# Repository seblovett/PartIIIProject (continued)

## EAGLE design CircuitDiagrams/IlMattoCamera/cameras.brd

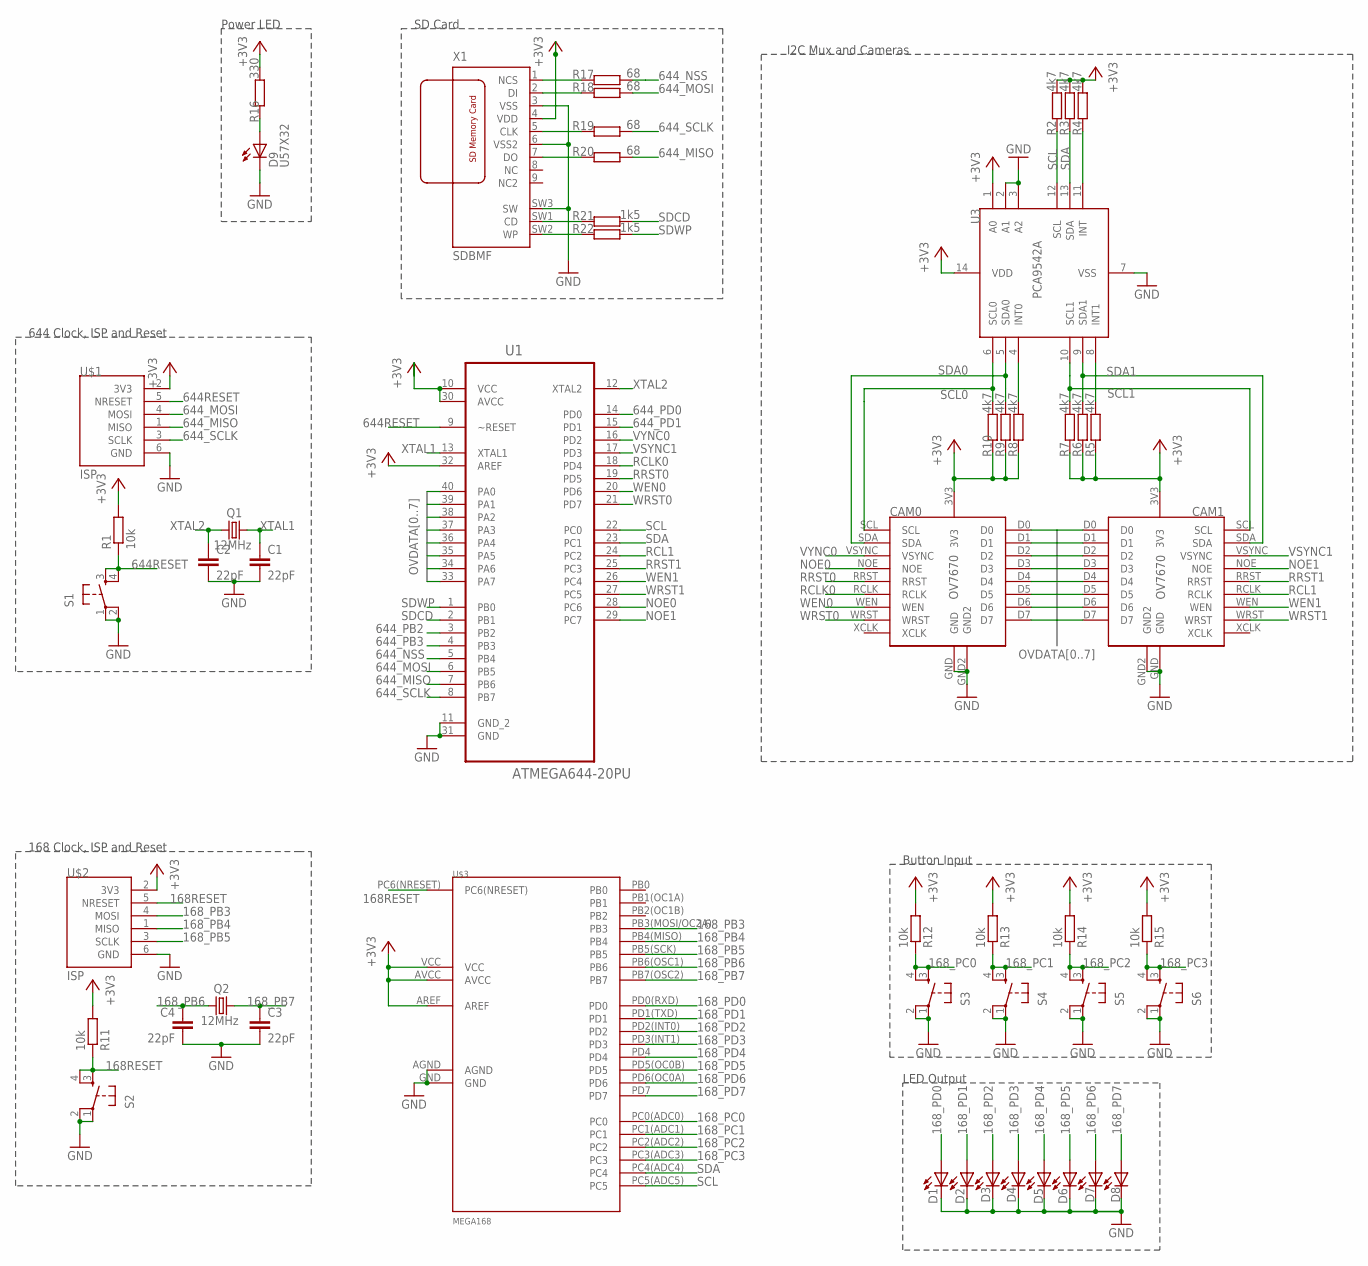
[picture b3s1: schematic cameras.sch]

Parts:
C1, C2, C3, C4: 22pF; C025-040X050
CAM0, CAM1: OV7670
D1, D2, D3, D4, D5, D6, D7, D8, D9: U57X32
Q1, Q2: 12MHz; HC49/S
R1, R11, R12, R13, R14, R15: 10k; 0204/7
R2, R3, R4, R5, R6, R7, R8, R9, R10: 4k7; 0204/7
R16: 330; 0204/7
R17, R18, R19, R20: 68; 0204/7
R21, R22: 1k5; 0204/7
S1, S2, S3, S4, S5, S6: TAC_SWITCHPTH; TACTILE-PTH
U1: ATMEGA644-20PU; DIP254P1524X482-40
U3: PCA9542A; TSSOP14
U$1, U$2: ISP; DUALHEAD_TH_6
U$3: MEGA168
X1: SDBMF; SDBMF-009XXBXX2

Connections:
168RESET: R11.1, S2.3, S2.4, U$2.5 (NRESET), U$3.PC6(NRESET)
168_PB3: U$2.4 (MOSI), U$3.PB3(MOSI/OC2A) (PB3)
168_PB4: U$2.1 (MISO), U$3.PB4(MISO) (PB4)
168_PB5: U$2.3 (SCLK), U$3.PB5(SCK) (PB5)
168_PB6: C4.1, Q2.1, U$3.PB6(OSC1) (PB6)
168_PB7: C3.1, Q2.2, U$3.PB7(OSC2) (PB7)
168_PC0: R12.1, S3.3, S3.4, U$3.PC0(ADC0) (PC0)
168_PC1: R13.1, S4.3, S4.4, U$3.PC1(ADC1) (PC1)
168_PC2: R14.1, S5.3, S5.4, U$3.PC2(ADC2) (PC2)
168_PC3: R15.1, S6.3, S6.4, U$3.PC3(ADC3) (PC3)
168_PD0: D1.A, U$3.PD0(RXD) (PD0)
168_PD1: D2.A, U$3.PD1(TXD) (PD1)
168_PD2: D3.A, U$3.PD2(INT0) (PD2)
168_PD3: D4.A, U$3.PD3(INT1) (PD3)
168_PD4: D5.A, U$3.PD4
168_PD5: D6.A, U$3.PD5(OC0B) (PD5)
168_PD6: D7.A, U$3.PD6(OC0A) (PD6)
168_PD7: D8.A, U$3.PD7
644RESET: R1.1, S1.3, S1.4, U1.9 (~RESET), U$1.5 (NRESET)
644_MISO: R20.1, U1.7 (PB6), U$1.1 (MISO)
644_MOSI: R18.1, U1.6 (PB5), U$1.4 (MOSI)
644_NSS: R17.1, U1.5 (PB4)
644_PB2: U1.3 (PB2)
644_PB3: U1.4 (PB3)
644_PD0: U1.14 (PD0)
644_PD1: U1.15 (PD1)
644_SCLK: R19.1, U1.8 (PB7), U$1.3 (SCLK)
+3V3: CAM0.3V3, CAM1.3V3, R1.2, R2.2, R3.2, R4.2, R5.1, R6.1, R7.1, R8.1, R9.1, R10.1, R11.2, R12.2, R13.2, R14.2, R15.2, R16.2, U1.10 (VCC), U1.30 (AVCC), U1.32 (AREF), U3.1 (A0), U3.14 (VDD), U$1.2 (3V3), U$2.2 (3V3), U$3.AREF, U$3.AVCC, U$3.VCC, X1.4 (VDD)
GND: C1.2, C2.2, C3.2, C4.2, CAM0.GND, CAM0.GND2, CAM1.GND, CAM1.GND2, D1.K (C), D2.K (C), D3.K (C), D4.K (C), D5.K (C), D6.K (C), D7.K (C), D8.K (C), D9.K (C), S1.1, S1.2, S2.1, S2.2, S3.1, S3.2, S4.1, S4.2, S5.1, S5.2, S6.1, S6.2, U1.11 (GND_2), U1.31 (GND), U3.2 (A1), U3.3 (A2), U3.7 (VSS), U$1.6 (GND), U$2.6 (GND), U$3.AGND, U$3.GND, X1.3 (VSS), X1.6 (VSS2), X1.SW3 (SW)
unnamed: R5.2, U3.8 (INT1)
unnamed: R8.2, U3.4 (INT0)
unnamed: R4.1, U3.11 (INT)
unnamed: R17.2, X1.1 (NCS)
unnamed: R18.2, X1.2 (DI)
unnamed: D9.A, R16.1
unnamed: R19.2, X1.5 (CLK)
unnamed: R20.2, X1.7 (DO)
unnamed: R21.2, X1.SW1 (CD)
unnamed: R22.2, X1.SW2 (WP)
NOE0: CAM0.NOE, U1.28 (PC6)
NOE1: CAM1.NOE, U1.29 (PC7)
OVDATA0: CAM0.D0, CAM1.D0, U1.40 (PA0)
OVDATA1: CAM0.D1, CAM1.D1, U1.39 (PA1)
OVDATA2: CAM0.D2, CAM1.D2, U1.38 (PA2)
OVDATA3: CAM0.D3, CAM1.D3, U1.37 (PA3)
OVDATA4: CAM0.D4, CAM1.D4, U1.36 (PA4)
OVDATA5: CAM0.D5, CAM1.D5, U1.35 (PA5)
OVDATA6: CAM0.D6, CAM1.D6, U1.34 (PA6)
OVDATA7: CAM0.D7, CAM1.D7, U1.33 (PA7)
RCL1: CAM1.RCLK, U1.24 (PC2)
RCLK0: CAM0.RCLK, U1.18 (PD4)
RRST0: CAM0.RRST, U1.19 (PD5)
RRST1: CAM1.RRST, U1.25 (PC3)
SCL: R2.1, U1.22 (PC0), U3.12 (SCL), U$3.PC5(ADC5) (PC5)
SCL0: CAM0.SCL, R10.2, U3.6 (SCL0)
SCL1: CAM1.SCL, R7.2, U3.10 (SCL1)
SDA: R3.1, U1.23 (PC1), U3.13 (SDA), U$3.PC4(ADC4) (PC4)
SDA0: CAM0.SDA, R9.2, U3.5 (SDA0)
SDA1: CAM1.SDA, R6.2, U3.9 (SDA1)
SDCD: R21.1, U1.2 (PB1)
SDWP: R22.1, U1.1 (PB0)
VSYNC1: CAM1.VSYNC, U1.17 (PD3)
VYNC0: CAM0.VSYNC, U1.16 (PD2)
WEN0: CAM0.WEN, U1.20 (PD6)
WEN1: CAM1.WEN, U1.26 (PC4)
WRST0: CAM0.WRST, U1.21 (PD7)
WRST1: CAM1.WRST, U1.27 (PC5)
XTAL1: C1.1, Q1.2, U1.13 (XTAL1)
XTAL2: C2.1, Q1.1, U1.12 (XTAL2)

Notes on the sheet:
Power LED
SD Card
644 Clock, ISP and Reset
168 Clock, ISP and Reset
Button Input
LED Output
I2C Mux and Cameras

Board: 2 copper layers, 51 parts (0 on the bottom side), 65 nets, no tracks yet.

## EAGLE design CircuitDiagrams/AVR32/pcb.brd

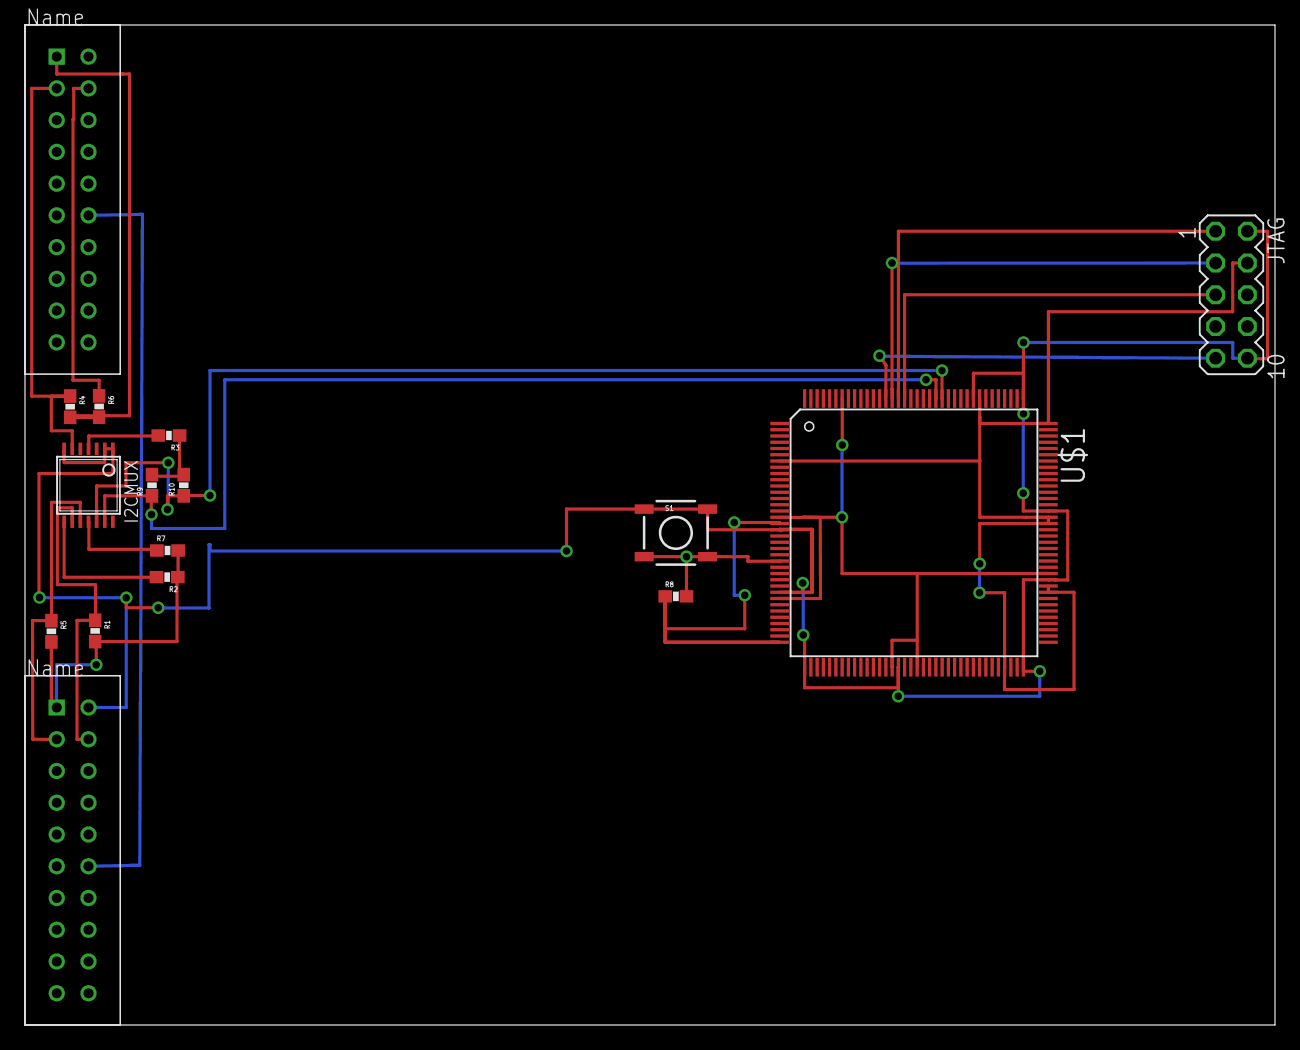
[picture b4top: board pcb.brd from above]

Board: 2 copper layers, 100.0 x 80.0 mm, 16 parts (0 on the bottom side), 18 nets.

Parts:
I2CMUX: PCA9542A; TSSOP14
JTAG: MA05-2
OV0, OV1: OV7670
R1, R2, R3, R4, R5, R6, R7, R9, R10: 4k7; 0603-RES
R8: 10k; 0603-RES
S1: TACTILE_SWITCH_SMD
U$1: AVR32UC3AVQFP144; VQFP144

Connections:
+3V3: I2CMUX.3, I2CMUX.5, I2CMUX.14, JTAG.4, OV0.SDA, OV1.3V3, R1.2, R2.1, R3.1, R5.2, R6.1, R7.2, R8.1, R9.2, R10.2, U$1.7, U$1.17, U$1.36, U$1.69, U$1.81, U$1.82, U$1.92, U$1.93, U$1.108, U$1.116
GND: I2CMUX.1, I2CMUX.2, I2CMUX.7, JTAG.2, JTAG.10, OV0.GND, OV1.GND, S1.1, S1.2, U$1.8, U$1.18, U$1.28, U$1.37, U$1.52, U$1.72, U$1.83, U$1.94, U$1.109, U$1.117
GND2: OV0.GND2, OV1.GND2
unnamed: I2CMUX.6, OV0.SCL, R4.1
unnamed: U$1.16, U$1.29, U$1.51, U$1.55, U$1.84, U$1.138
unnamed: OV0.3V3, R4.2, R6.2
unnamed: R8.2, S1.3, S1.4, U$1.23
unnamed: I2CMUX.9, OV1.SDA, R1.1
unnamed: I2CMUX.10, OV1.SCL, R5.1
unnamed: JTAG.1, U$1.129
unnamed: JTAG.3, U$1.130
unnamed: JTAG.5, U$1.128
unnamed: I2CMUX.8, R2.2
unnamed: I2CMUX.4, R3.2
unnamed: JTAG.9, U$1.131
unnamed: I2CMUX.11, R7.1
SCL: I2CMUX.12, R10.1, U$1.122
SDA: I2CMUX.13, R9.1, U$1.123

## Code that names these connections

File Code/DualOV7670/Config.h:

/*
 * Config.h
 *
 * Created: 25/10/2012 21:58:56
 *  Author: hslovett
 */ 
#define F_CPU 12000000UL
#include <avr/io.h>
#include <avr/interrupt.h>
#include <avr/pgmspace.h>
#include <stdio.h>
#include <stdlib.h>
#include <string.h>
#include <util/delay.h>
#include "TWI_Master.h"
#include "ff.h"
#include "diskio.h"
#include "Bitmap.h"
#include "DualCameras.h"
#include "PCA9542A.h"
#ifndef CONFIG_H_
#define CONFIG_H_


void IO_Init(void);

#define TRUE 1
#define FALSE 0

FIL Files[2];
char Buff[1024];

#define BMPFileSize		153738
#define RGBFileSize		153600
//////////////////////////////////////////////////////////////////////////
//	Port A
//////////////////////////////////////////////////////////////////////////
#define FIFO_AVR_DPRT		DDRA
#define FIFO_AVR_PORT		PORTA
#define FIFO_AVR_PINP		PINA
//////////////////////////////////////////////////////////////////////////
//	Port B
//////////////////////////////////////////////////////////////////////////
#define SD_WP			PB0
#define SD_CD			PB1
//#define 				PB2
//#define 				PB3
#define SPI_nSS_SD		PB4
#define SPI_MOSI		PB5
#define SPI_MISO		PB6
#define SPI_SCK			PB7
//////////////////////////////////////////////////////////////////////////
//	Port C
//////////////////////////////////////////////////////////////////////////
#define TWI_SCL			PC0
#define TWI_SDA			PC1
#define FIFO_RCLK_1		PC2
#define FIFO_nRRST_1	PC3
#define FIFO_WEN_1		PC4
#define FIFO_WRST_1		PC5
#define FIFO_nOE_0		PC6
#define FIFO_nOE_1		PC7
//////////////////////////////////////////////////////////////////////////
//	Port D
//////////////////////////////////////////////////////////////////////////
#define USART0_RX		PD0
#define USART0_TX		PD1
#define OV7670_VSYNC_0	PD2	//MUST BE AN INTERRUPT PIN
#define OV7670_VSYNC_1	PD3	//MUST BE AN INTERRUPT PIN
#define FIFO_RCLK_0		PD4
#define FIFO_nRRST_0	PD5
#define FIFO_WEN_0		PD6
#define FIFO_WRST_0		PD7



#endif /* CONFIG_H_ */

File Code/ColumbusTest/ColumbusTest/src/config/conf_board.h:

/**
 * \file
 *
 * \brief User board configuration template
 *
 */

#ifndef CONF_BOARD_H
#define CONF_BOARD_H

//Clock
#define FOSC0           16000000                                //!< Osc0 frequency: Hz.
#define OSC0_STARTUP    AVR32_SCIF_OSCCTRL0_STARTUP_2048_RCOSC  //!< Osc0 startup time: RCOsc periods.

#define BOARD_OSC0_HZ           16000000
#define BOARD_OSC0_STARTUP_US   2000
#define BOARD_OSC0_IS_XTAL      true
#define BOARD_OSC32_HZ          32768
#define BOARD_OSC32_STARTUP_US  71000
#define BOARD_OSC32_IS_XTAL     true


//SDRAM 

//! Part header file of used SDRAM(s).
#define SDRAM_PART_HDR  "mt48lc16m16a2tg7e/mt48lc16m16a2tg7e.h"

//! Data bus width to use the SDRAM(s) with (16 or 32 bits; always 16 bits on
//! UC3).
#define SDRAM_DBW       16

//USB


/*! \name USB Definitions
 */
//! @{
//! Multiplexed pin used for USB_ID: AVR32_USBC_ID_x.
//! To be selected according to the AVR32_USBC_ID_x_PIN and
//! AVR32_USBC_USB_ID_FUNCTION definitions from <avr32/uc3cxxxx.h>.
#define USB_ID                             AVR32_USBC_ID_

//! Multiplexed pin used for USB_VBOF: AVR32_USBC_VBOF_x.
//! To be selected according to the AVR32_USBC_VBOF_x_PIN and
//! AVR32_USBC_USB_VBOF_FUNCTION definitions from <avr32/uc3cxxxx.h>.
#define USB_VBOF                           AVR32_USBC_VBOF

//! Active level of the USB_VBOF output pin.
# define USB_VBOF_ACTIVE_LEVEL       LOW

//! USB overcurrent detection pin.
# define USB_OVERCURRENT_DETECT_PIN  AVR32_PIN_PB7



//LEDs
//! Number of LEDs.
#define LED_COUNT   6

/*! \name GPIO Connections of LEDs
 */
//! @{
#define LED_MOTOR	AVR32_PIN_PB12
#define LED2_GPIO   AVR32_PIN_PB17
#define LED3_GPIO   AVR32_PIN_PB18
#define LED4_GPIO   AVR32_PIN_PB27
#define LED5_GPIO   AVR32_PIN_PB28
#define LED6_GPIO   AVR32_PIN_PB29

#define LED2_SET {gpio_set_gpio_pin(LED2_GPIO);}
#define LED3_SET {gpio_set_gpio_pin(LED3_GPIO);}
#define LED4_SET {gpio_set_gpio_pin(LED4_GPIO);}
#define LED5_SET {gpio_set_gpio_pin(LED5_GPIO);}
#define LED6_SET {gpio_set_gpio_pin(LED6_GPIO);}
#define LEDMOTOR_SET {gpio_set_gpio_pin(LED_MOTOR);}

#define LED2_CLR {gpio_clr_gpio_pin(LED2_GPIO);}
#define LED3_CLR {gpio_clr_gpio_pin(LED3_GPIO);}
#define LED4_CLR {gpio_clr_gpio_pin(LED4_GPIO);}
#define LED5_CLR {gpio_clr_gpio_pin(LED5_GPIO);}
#define LED6_CLR {gpio_clr_gpio_pin(LED6_GPIO);}
#define LEDMOTOR_CLR {gpio_clr_gpio_pin(LED_MOTOR);}


//Motors
#define MOTOR_L_STBY	AVR32_PIN_PB08
#define MOTOR_L_IN1		AVR32_PIN_PB09
#define MOTOR_L_IN2		AVR32_PIN_PB10
#define MOTOR_L_PWM		AVR32_PIN_PB11

#define MOTOR_R_STBY	AVR32_PIN_PB16
#define MOTOR_R_IN1		AVR32_PIN_PB15
#define MOTOR_R_IN2		AVR32_PIN_PB14
#define MOTOR_R_PWM		AVR32_PIN_PB13

//PWM
// #  define M0_PWM_L_PIN             AVR32_PWM_PWML_0_1_PIN
// #  define M0_PWM_L_FUNCTION        AVR32_PWM_PWML_0_1_FUNCTION
#  define ML_PWM_H_PIN             AVR32_PWM_PWMH_1_1_PIN
#  define ML_PWM_H_FUNCTION        AVR32_PWM_PWMH_1_1_FUNCTION
#  define ML_PWM_CHANNEL_ID        1
#  define MR_PWM_H_PIN             AVR32_PWM_PWMH_2_2_PIN
#  define MR_PWM_H_FUNCTION        AVR32_PWM_PWMH_2_2_FUNCTION
#  define MR_PWM_CHANNEL_ID        2

//Macros
#define ML_STANDBY		{gpio_clr_gpio_pin(MOTOR_L_STBY);}
#define ML_GO			{gpio_set_gpio_pin(MOTOR_L_STBY);}
#define ML_IN1_SET		{gpio_set_gpio_pin(MOTOR_L_IN1);}
#define ML_IN2_SET		{gpio_set_gpio_pin(MOTOR_L_IN2);}
#define ML_IN1_CLR		{gpio_clr_gpio_pin(MOTOR_L_IN1);}
#define ML_IN2_CLR		{gpio_clr_gpio_pin(MOTOR_L_IN2);}
// #define M0_PWM_HIGH		{gpio_set_gpio_pin(MOTOR_0_PWM);}
// #define M0_PWM_LOW		{gpio_clr_gpio_pin(MOTOR_0_PWM);}
	
#define MR_STANDBY		{gpio_clr_gpio_pin(MOTOR_R_STBY);}
#define MR_GO			{gpio_set_gpio_pin(MOTOR_R_STBY);}
#define MR_IN1_SET		{gpio_set_gpio_pin(MOTOR_R_IN1);}
#define MR_IN2_SET		{gpio_set_gpio_pin(MOTOR_R_IN2);}
#define MR_IN1_CLR		{gpio_clr_gpio_pin(MOTOR_R_IN1);}
#define MR_IN2_CLR		{gpio_clr_gpio_pin(MOTOR_R_IN2);}
// #define M1_PWM_HIGH		{gpio_set_gpio_pin(MOTOR_1_PWM);}
// #define M1_PWM_LOW		{gpio_clr_gpio_pin(MOTOR_1_PWM);}	
//SD Card

#define SD_MMC_SPI_MEM_CNT          1
#define SD_MMC_0_CD_GPIO            AVR32_PIN_PB26
#define SD_MMC_0_CD_DETECT_VALUE    1
#define SD_MMC_0_WP_GPIO            AVR32_PIN_PD30
#define SD_MMC_0_WP_DETECT_VALUE    0
#define SD_MMC_SPI_0_CS             0

// Keep it for SD MMC stack ASF V1.7
#define SD_MMC_CARD_DETECT_PIN      SD_MMC_0_CD_GPIO
#define SD_MMC_WRITE_PROTECT_PIN    SD_MMC_0_WP_GPIO
#define SD_MMC_SPI_NPCS             SD_MMC_SPI_0_CS

#define SD_MMC_SPI                  (&AVR32_SPI1)
#define SD_MMC_SPI_SCK_PIN          AVR32_SPI1_SCK_0_1_PIN
#define SD_MMC_SPI_SCK_FUNCTION     AVR32_SPI1_SCK_0_1_FUNCTION
#define SD_MMC_SPI_MISO_PIN         AVR32_SPI1_MISO_0_1_PIN
#define SD_MMC_SPI_MISO_FUNCTION    AVR32_SPI1_MISO_0_1_FUNCTION
#define SD_MMC_SPI_MOSI_PIN         AVR32_SPI1_MOSI_0_1_PIN
#define SD_MMC_SPI_MOSI_FUNCTION    AVR32_SPI1_MOSI_0_1_FUNCTION
#define SD_MMC_SPI_NPCS_PIN         AVR32_SPI1_NPCS_0_2_PIN
#define SD_MMC_SPI_NPCS_FUNCTION    AVR32_SPI1_NPCS_0_2_FUNCTION
//! \brief PBA clock frequency (Hz)
#define PBA_HZ                FOSC0

//! \brief Number of bytes in the receive buffer when operating in slave mode
#define BUFFERSIZE            64


#define AVR32_PDCA_CHANNEL_USED_RX AVR32_PDCA_PID_SPI1_RX
#define AVR32_PDCA_CHANNEL_USED_TX AVR32_PDCA_PID_SPI1_TX

#define AVR32_PDCA_CHANNEL_SPI_RX 0 // In the example we will use the pdca channel 0.
#define AVR32_PDCA_CHANNEL_SPI_TX 1 // In the example we will use the pdca channel 1.

//USART

#define DBG_USART                   (&AVR32_USART2)
#define DBG_USART_RX_PIN           AVR32_USART2_RXD_0_1_PIN
#define DBG_USART_RX_FUNCTION      AVR32_USART2_RXD_0_1_FUNCTION
#define DBG_USART_TX_PIN           AVR32_USART2_TXD_0_1_PIN
#define DBG_USART_TX_FUNCTION      AVR32_USART2_TXD_0_1_FUNCTION
#define DBG_USART_IRQ               AVR32_USART2_IRQ
#define DBG_USART_IRQ_GROUP         AVR32_USART2_IRQ_GROUP
#define DBG_USART_SYSCLK            SYSCLK_USART2
#define DBG_USART_BAUDRATE			57600


// static const usart_options_t USART_OPTIONS =
// 	{
// 		.baudrate     = 57600,
// 		.charlength   = 8,
// 		.paritytype   = USART_NO_PARITY,
// 		.stopbits     = USART_1_STOPBIT,
// 		.channelmode  = USART_NORMAL_CHMODE
// 	};

//Analogue Comparators
//Comparator A
#define POT0_AC1AP1_INPUT		1
#define POT0_AC1AP1_PIN			AVR32_AC1AP1_PIN
#define POT0_AC1AP1_FUNCTION	AVR32_AC1AP1_FUNCTION

#define SENSE0_AC1AN1_INPUT		1
#define SENSE0_AC1AN1_PIN		AVR32_AC1AN1_PIN
#define SENSE0_AC1AN1_FUNCTION	AVR32_AC1AN1_FUNCTION

//Comparator B
#define POT1_AC1BP1_INPUT		3
#define POT1_AC1BP1_PIN			AVR32_AC1BP1_PIN
#define POT1_AC1BP1_FUNCTION	AVR32_AC1BP1_FUNCTION

#define SENSE1_AC1BN1_INPUT		1
#define SENSE1_AC1BN1_PIN		AVR32_AC1BN1_PIN
#define SENSE1_AC1BN1_FUNCTION	AVR32_AC1BN1_FUNCTION
#endif // CONF_BOARD_H

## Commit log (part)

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2012-11-08 Added Research list
2012-11-08 Added Datasheets
2012-11-09 Started Dual camera code, firstly with one camera but pins swapped around. Image is taking, but AVR resets itself after image has been written to SD Card. Not yet found out why...
2012-11-10 Solved bug where the AVR resets itself after taking a photo
2012-11-12 started UI
2012-11-12 Update all files.
2012-11-13 Stereovision working. Colours in bitmap solved
2012-11-13 Added some pictures obtained from the device
2012-11-13 Updated to stereovision branch
2012-11-17 Added Matlab Directory for protoyping stereovision algorithms. Code now writes images labelled with Left and right
2012-11-17 Implemented a very poor non functional correlating function. Needs vastly improving.
2012-11-20 Starting Image rectification using built in MATLAB Commands
2012-11-20 Started some edge detection and image rectification algorithms
2012-11-21 Got a basic algorithm working!
2012-11-21 Got SSD matching working. Started on NCC. Need to improve rectification.
2012-11-22 added more research and a registration document
2012-11-23 Updated LaTeX Template
2012-11-25 Done a section in HardwareDevelopment and added some references
2012-11-27 Added some more photos and research articles. Archived off old MATLAB scripts.
2012-11-28 Done some more work on corner matching using SSD and cross correlation. Added more research articles
2012-11-29 Added a confidence test into the FindMatch script
2012-11-29 Did some more work on the hardware development section
2012-12-03 Update atsuo file
2012-12-03 Almost finished HardwareDevelopment, just a few things left to tweak
2012-12-03 Started comparison of image detection stuff. Far from completion
2012-12-03 Added figures and some text
2012-12-05 Did a lot of report. All that remains is intro, research, circuit diagram for current set up, range derivations and testing and conclusion. Word count bat file added. Added appendix C of code. Starte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
2012-12-05 Added dual camera circuit diagram and explain UI.
2012-12-05 Done some introduction and changed some formatting. Plus more references.
2012-12-05 Completed HardwareDevelopment and InvestigationVision. Need to do research and conclusion
2012-12-06 Completed First Draft!!
2012-12-06 Second Draft
2012-12-07 Corrected some mistakes and rewrote abstract
2012-12-07 Fourth Draft: Changed format, added some figures
2012-12-07 Draft 5. Changed some figures to make them look better.
2012-12-07 Seventh Draft. Formatted equations, particularly parenthesis. Tidied up figures.
2012-12-08 Ninth Draft. Read through all and made many minor changes. Added key to NCCResults.jpg
2012-12-08 Tenth Draft
2012-12-10 Report Final. Short Report also added
2012-12-11 Started Circuit schematic
2012-12-12 Started motor driver prototype
2012-12-15 Done some work on Motor Driver code.
2012-12-18 Proportional controller implemented
2012-12-18 Added some comments to motor code
2012-12-18 Done some more to the PCB. Worked out how to use the cam2print script
2012-12-20 Done some more on PCB, mainly adding decoupling capacitors (lots of)
2012-12-20 Added UC3C Datasheet
2012-12-22 Wired up GPIOs to Devices. Need to add a UI.
2012-12-22 Changed JTAG Connection to include the Reset Pin.
2012-12-23 Completed First Draft of Schematic
2012-12-24 Changed the JTAG Package. Added Headers for all unused pins.
2012-12-24 Half way through routing the GND Connections
2012-12-25 Finished Wiring GND. Done USB Data and oscillator
2012-12-25 Ripped up SDRAM lines due to poor routing. Working on it again
2012-12-26 Routed the SDRAM
2012-12-26 Routed Camera Data Bus
2012-12-31 Routed Camera Control Lines
2012-12-31 Routed SPI and UART. Added GND to SPI Header
2012-12-31 Routed Motor LED and other motor driver
2012-12-31 Routed LEDs
2013-01-09 Sorting Keepout Errors. 96 to go!
2013-01-09 Corrected all keepout errors!
2013-01-14 Missed an Airwire on PCB
2013-01-22 The Columbus is now complete and sent of. This is the ACTUAL final version
2013-01-28 Changed some via holes and put things on the correct layer for the silkscreen
2013-02-09 Done some report stuff.
2013-02-09 Report.pdf changed
2013-02-10 Done SDRAM Test, but still not working. Carrying on with other parts and will come back to this
2013-02-10 SD Card Test working
2013-02-10 Moved SD Card methods to own files to neaten up
2013-02-10 TWI Test Done
2013-02-12 Added all new files in...
2013-02-12 Got basic forward and backward motor movement working
2013-02-12 Got bootloader working and added a bat to program it using it
2013-02-14 Added analogue comparator
2013-02-14 Analogue comparators work by poling. Moving to make this interrupt based
2013-02-15 Got motors to reset to interrupt tabs!
2013-02-15 Got I2C Mux working and selecting channels. Camera can be found on channel 1 (right) but not got a socket for camera 0 (left)
2013-02-16 Connected VSYNC0 to PA10 - EXTINT4, to get it to work to to special aspects of EXTINT0
2013-02-16 Got interrupts working so that a frame of data can be obtained
2013-02-16 Added a method to write numbers to the log file
2013-02-17 Got images storing to SD card, but the second image taken, colours don't appear correctly. Something to do with Bus contention?
2013-02-17 Got both images taking and storing properly!! Needed to reset individual FIFO buffers before progressing
2013-02-18 All parts activated. Motors had some problems, so diabled VSYNC interrupts when not in use and re tipexed the wheels
2013-02-18 Solved numbering issue.
2013-02-21 Done Matlab code to show phase and magnatude of an image. Starting development in C
2013-02-25 Got RAM sort of working...
2013-02-26 Added USB Virtual COM Port support, so no need for extra uart cable
2013-02-26 Cameras weren't working, changed enable interrupt lines around to solve
2013-02-27 Removed the testing side of everything.
2013-02-28 Added a link to a document about using SDRAM on AT32
2013-02-28 Made so SDRAM is DMA. Can create variables in it. Also impletmented a System Test
2013-03-01 Got some sort of Fourier Transform working. Need to check and expand
2013-03-04 Got 1D FFT working
2013-03-05 Cameras are working again. Don't know what was wrong and haven't changed anything (apart from uncommenting the system test to stop the system from stopping on error)
2013-03-05 Added a help prompt. Got reading in integers, big endian. Want to create a file format so this can be done dynamically. i.e. endian, uint8/int32 etc.
2013-03-07 Moved 1D FFT Function to ImageProcessor.c. Uses predefined size but works. Moving on to 2D now
2013-03-07 Implemented a 2DFFT, however only have the real to complex method with 32 bit fixed point. Going to swap to 16bit fixed point
2013-03-07 Got 2D FFT working! Problem occured as methods scale. Multiplied up afterwards and all is good!
2013-03-10 Started image preparation, but noticed the taking of photos is not working properly now. Going to look into this..
2013-03-11 Write BMP method written. Need to work out what is wrong with the write pointer before I can test properly, but it seems to work.
2013-03-12 Converted to a dedicated BMP writing method.
2013-03-13 Re-added the code to disable and enable interrupts of the VSYNC signal from the cameras.
2013-03-14 Protyped a 2d IFFT. Need to test it
2013-03-14 Added ComplexMultiply method to dot multiply two arrays of complex numbers together. Will be used to NCC
2013-03-15 Changed so that the save method takes a uin16 array. A better standard for throwing information around. Will no doubt have to change something when it comes to storing grey scale
2013-03-15 Attempted to implement a prepare image method. Doesn't seem to work... Moving on the movement things!
2013-03-18 Added rotating code. Not tested
2013-03-18 Renamed the Interim Report Files
2013-03-18 Added Results Section to report. Removed some outdated parts from report which were for Interim only and also added sections and notes to complete
2013-03-19 Added some figures and an explanation of Motor Driving. Moving on to testing
2013-03-19 Changed some of the Motor Driver code. Still got noise issues
2013-03-19 Done some writing on PCB development and added figures of circuit and PCB.
2013-03-20 Test program changed to not use the USB COM Port and more in depth testing done
2013-03-20 Removed files for USB COM Port in Columbus \Tester
2013-03-20 Almost completed Hardware Development. Need to do motor test and overall conclusion
2013-03-20 Updated hierarchy diagram
2013-03-21 Planned out Vision Section
2013-03-21 Done Fourier Transform section. Need to move on to 2D FFT now
2013-03-22 Added contents file (needs completing) and relevant appendix that reads from Contents.txt. Done some on 2D FFT
2013-03-22 Started on the Low level algorithms section
2013-03-22 Added Results.tex to word counter
2013-03-22 Removed unused Eagle files
2013-03-23 Renamed appendicies and changed their order. Also removed log files that were created by mistake
2013-03-23 Small modifications to CSV read/write. Also to 1D FFT to denormalise the results.
2013-03-23 Added saving of complex array to CSV
2013-03-23 Started looking at rectangular pulse test, but doesn't look too nice at the moment.
2013-03-24 Done rectangular pulse test. Reduced the position of the decimal point in fixed point
2013-03-25 Obtained data and generated figures for 2D FFT Test. Need to do comparison
2013-03-25 Done lots of FT stuff and added code for time testing
2013-03-26 Finished Fourier side of things. Just need to conclude. Started on Motor again
2013-03-26 Some small tweaks of the report. Moving on to motor
2013-03-26 Edited some small things
2013-03-27 Done Motor testing and completed Hardware Development section. Need to ammend some figures and maybe test rotating of the motors.
2013-04-02 Ammended some small mistakes and started on conclusion
2013-04-02 Changed motor move methods to return the distances moved
2013-04-02 Done the barebones of abstract and conclusion
2013-04-02 Added to Conclusion. Modified make.bat to do a WordCount and update the dropbox
2013-04-03 Lots of minor changes done
2013-04-03 Recomplied.
2013-04-04 Some minor changes
2013-04-05 First draft. At 10032 words. Included some simple range finding testing
2013-04-05 Done Distance test. Results in Distance_Data.m
2013-04-06 Complete Range testing. Added to conclusion.
2013-04-06 Done some more for autorun
2013-04-07 Got AutoRun loading from text file
2013-04-07 Added methods to run autorun commands. Need to test
2013-04-07 Got AutoRun working. Added indication LEDs.
2013-04-08 Small clean ups in code. Spell Checked report.
2013-04-09 Added a global image number counter stored on the SD card as Flash was not playing ball
2013-04-10 Added a figure of the back of the camera
2013-04-11 Changed a figure
2013-04-11 Recompd. Attempted to 2Up Appendix.
2013-04-12 Doing contents. Removing a lot of unused items that have no relevance
2013-04-12 Changed another figure. Tidied up the Matlab folder. Added the SDCard contents
2013-04-13 Added a Field of View figure
2013-04-13 Added FoV.jpg to the commit. Added a start to the ASM
2013-04-13 Set up TeXCount properly...
2013-04-13 Ammeded label issue
2013-04-13 Redone some FFT from AVR graphs.
2013-04-14 Improved Project management section. Added some more Gantt Charts and corrected some table captions
2013-04-14 Added first half of Alice's corrections. Second half yet to arrive.
2013-04-14 Added code for Il Matto and TFT Screen
2013-04-14 Added Statement of Originality
2013-04-15 Added nomenclature
2013-04-15 Added some more for list of abbreviations
2013-04-18 Changed font style of word MATLAB in report
2013-04-23 Changed tables so that they have bold headings.
2013-04-24 Changed EAGLE figures to PDF format to look nicer. Ammended a few minor mistakes
2013-04-25 Added EAGLE files for Il Matto Dual Camera sschematic
2013-04-25 Updated Appendix_Contents.tex
2013-04-26 Sorted some tables in the appendix out.
2013-04-26 Spell Checked report
2013-04-26 Changed a picture. Small modifications done
2013-04-26 Added some MATLAB data files for results
2013-04-29 Small modifications. Almost there...
2013-04-29 Small change and recompile
2013-04-29 Added some changes suggested by Toby.
2013-04-29 Ammeded Contents of files to Contents of Design Archive
